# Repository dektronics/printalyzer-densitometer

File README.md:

# Printalyzer Densitometer

## Introduction

The Printalyzer Densitometer is a project whose goal is the creation of an
affordable reflection and transmission densitometer for photographic darkroom
use.

It was initially conceived as an accessory to complement the
[Printalyzer Enlarging Timer & Exposure Meter](https://github.com/dektronics/printalyzer-timer)
to ease the process of creating paper profiles. However, given the general
utility of such a device, it has been spun off as a separate project in its
own right.

A good overview of the project can be found in these blog posts:
* [The Printalyzer Densitometer Project](https://hecgeek.blogspot.com/2021/07/the-printalyzer-densitometer-project.html)

This project, using hardware tagged as "Revision C" and labeled as DPD-100, is currently shipping as an official Dektronics [product](https://www.dektronics.com/printalyzer-densitometer). Links to the user manual and regulatory compliance documents can be found on the product website.

## Project Layout

### Hardware
The "hardware" directory contains [KiCad](https://www.kicad.org/) projects
with the complete circuit schematics, bill-of-materials, and
PCB layouts.

### Software
The "software" directory contains all the source code for the firmware
that runs on the hardware.

### Enclosure
The "enclosure" directory contains any CAD models and related resources
necessary to physically assemble the device.

## License
Individual directories will contain LICENSE files as needed, with relevant
details. Generally, the hardware will be CC BY-SA and the software will be
BSD 3-Clause. However, external resources may have their own individual license terms.

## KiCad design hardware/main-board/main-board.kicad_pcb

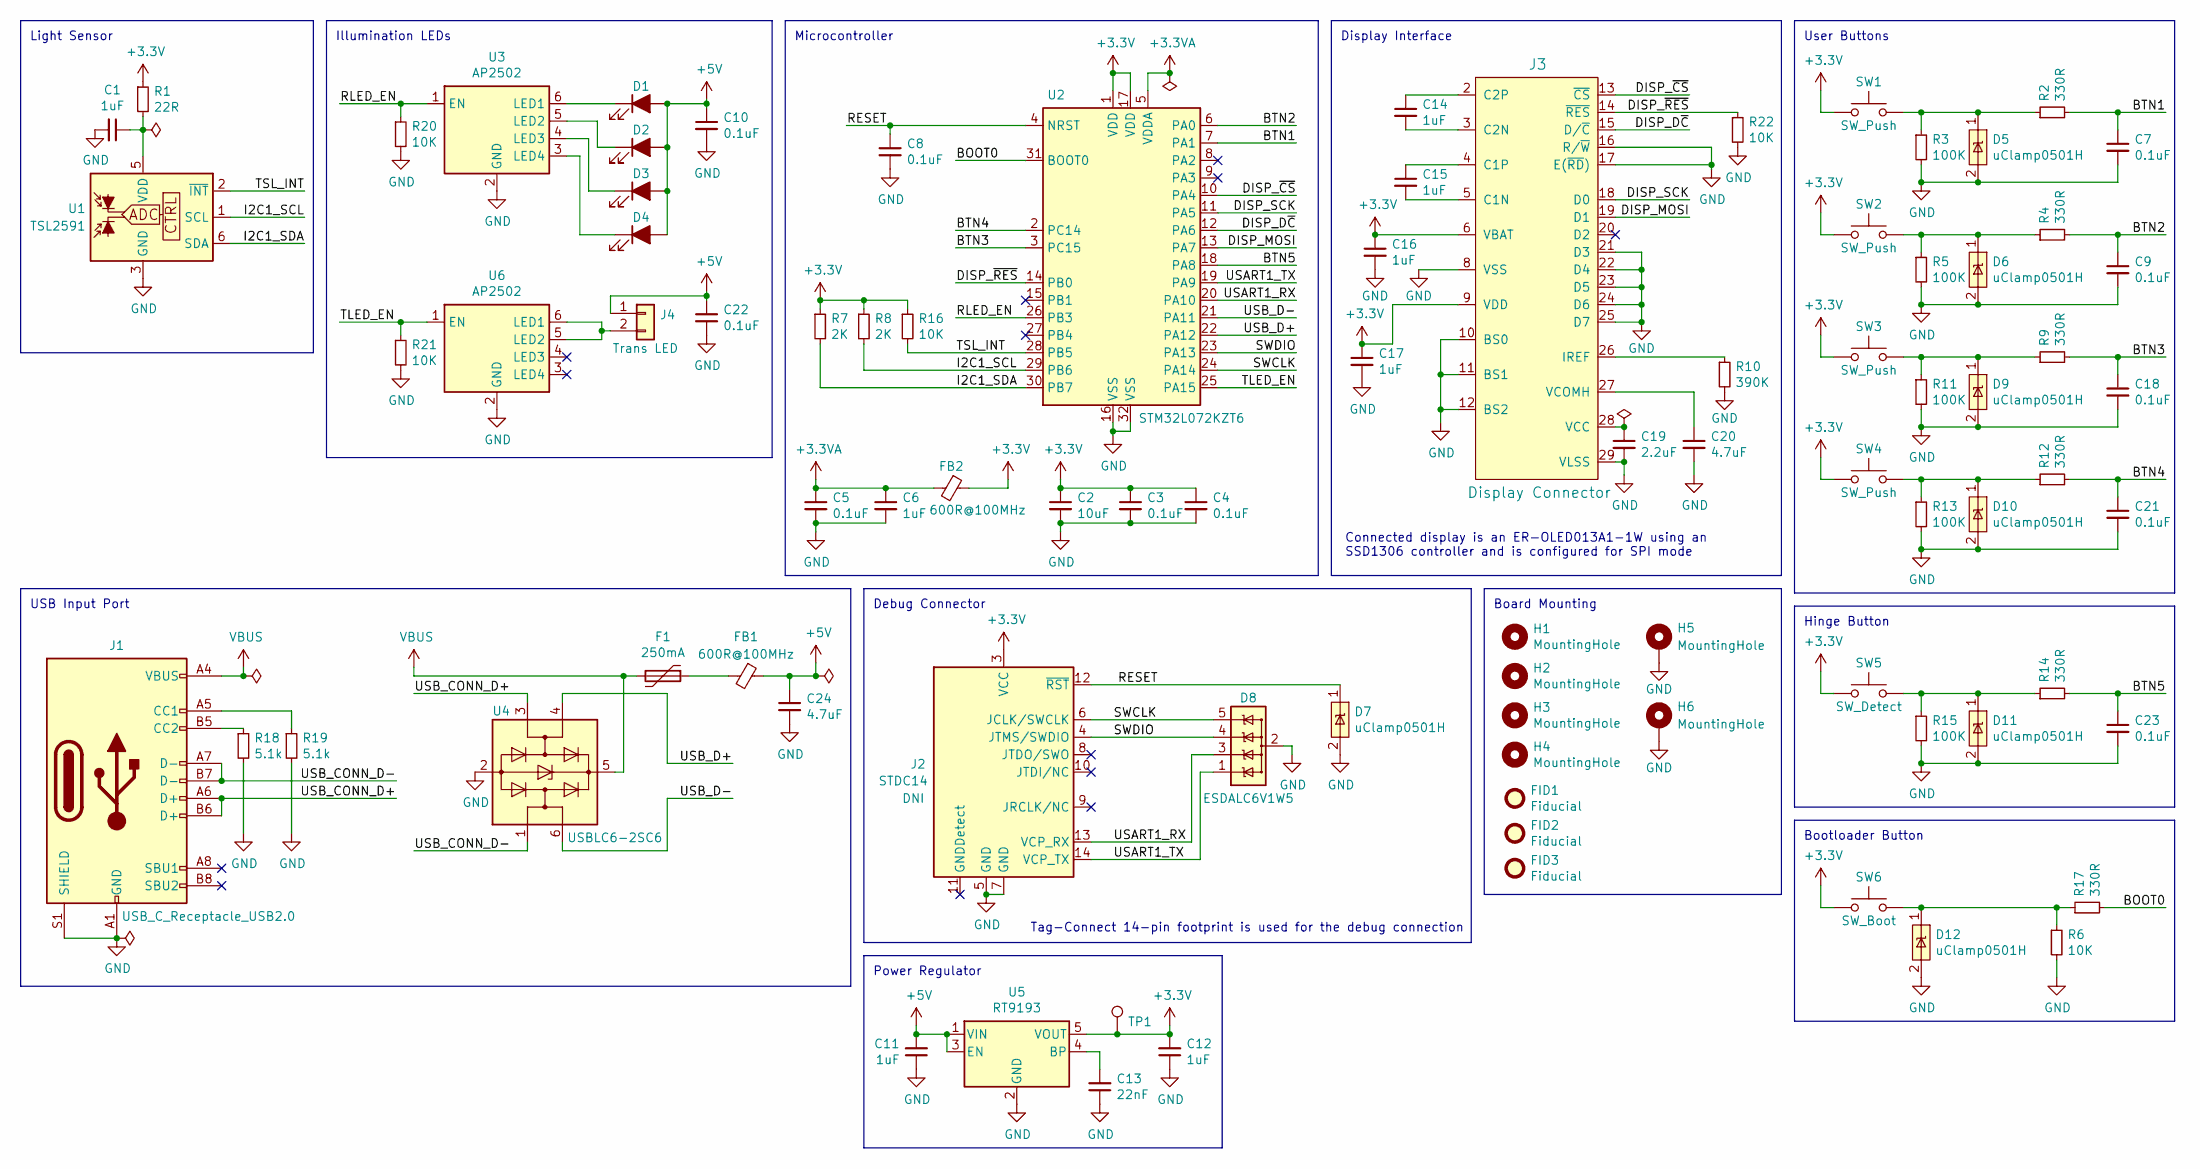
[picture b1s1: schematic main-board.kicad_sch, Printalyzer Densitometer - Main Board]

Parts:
C1: 1uF; C_0402_1005Metric; Manufacturer PN CL05A105KQ5NNNC
C2: 10uF; C_0805_2012Metric; Manufacturer PN CL21A106KAYNNNE
C3, C4, C5, C7, C8, C9, C10, C18, C21, C22, C23: 0.1uF; C_0603_1608Metric; Manufacturer PN CL10B104KA8NNNC
C6, C11, C12, C14, C15, C16, C17: 1uF; C_0603_1608Metric; Manufacturer PN CL10B105KA8NNNC
C13: 22nF; C_0805_2012Metric; Manufacturer PN C2012C0G1H223JT000N
C19: 2.2uF; C_0603_1608Metric; Manufacturer PN CL10B225KP8NNNC
C20, C24: 4.7uF; C_0603_1608Metric; Manufacturer PN CL10A475KA8NQNC
D1, D2, D3, D4: LED; LED_WL-SWTP-3022-1MP; Manufacturer PN 158302250
D5, D6, D7, D9, D10, D11, D12: uClamp0501H; D_SOD-523; Manufacturer PN UCLAMP0501H.TCT
D8: ESDALC6V1W5; SOT323-5L; Manufacturer PN ESDALC6V1W5
F1: 250mA; BF_0ZCJ_1206; Manufacturer PN 1206L025YR
FB1, FB2: 600R@100MHz; L_0603_1608Metric; Manufacturer PN MMZ1608B601CTAH0
FID1, FID2, FID3: Fiducial; Fiducial_1mm_Mask2mm
H1, H2, H3, H4: MountingHole; MountingHole_2.2mm_M2
H5, H6: MountingHole; MountingHole_2.2mm_M2_Pad_Via
J1: USB_C_Receptacle_USB2.0; USB_C_Receptacle_GCT_USB4105; Manufacturer PN USB4105-GF-A
J2: DNI; Tag-Connect_TC2070-IDC-FP_2x07_P1.27mm_Vertical; Manufacturer PN TC2070-IDC-050
J3: Display Connector; ER-CON30HT-1; Manufacturer PN ER-CON30HT-1
J4: Conn_01x02; JST_SH_BM02B-SRSS-TB_1x02-1MP_P1.00mm_Vertical; Manufacturer PN BM02B-SRSS-TB(LF)(SN)
R1: 22R; R_0402_1005Metric; Manufacturer PN AC0402JR-0722RL
R2, R4, R9, R12, R14, R17: 330R; R_0603_1608Metric; Manufacturer PN RC0603JR-07330RL
R3, R5, R11, R13, R15: 100K; R_0603_1608Metric; Manufacturer PN RC0603JR-07100KL
R6, R16, R20, R21, R22: 10K; R_0603_1608Metric; Manufacturer PN RC0603JR-0710KL
R7, R8: 2K; R_0603_1608Metric; Manufacturer PN CRCW06032K00JNEA
R10: 390K; R_0603_1608Metric; Manufacturer PN RC0603FR-07390KL
R18, R19: 5.1k; R_0603_1608Metric; Manufacturer PN RC0603JR-075K1L
SW1, SW2, SW3, SW4: SW_Push; ESwitch_TL1105_6mm_H7.5mm; Manufacturer PN TL1105SPF160Q
SW5: SW_Detect; CK_KSU213WLFG; Manufacturer PN KSU213WLFG
SW6: SW_Boot; Panasonic_EVQP7C_EVQP7L; Manufacturer PN EVQ-P7L01P
TP1: 3.3V; TestPoint_Pad_D2.0mm
U1: TSL2591; AMS_TSL2591; Manufacturer PN TSL25911FN
U2: STM32L072KZT6; ST_LQFP32; Manufacturer PN STM32L072KZT6
U3, U6: AP2502; SOT-23-6; Manufacturer PN AP2502KTR-G1
U4: USBLC6-2SC6; SOT-23-6; Manufacturer PN USBLC6-2SC6
U5: RT9193; SOT-23-5; Manufacturer PN RT9193-33GB

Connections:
+3.3V: C2.1, C3.1, C4.1, C12.2, C16.1, C17.1, FB2.1, J2.3 (VCC), J3.6 (VBAT), J3.9 (VDD), R1.1, R7.1, R8.1, R16.1, SW1.1, SW2.1, SW3.1, SW4.1, SW5.1, SW6.1, TP1.1, U2.1 (VDD), U2.17 (VDD), U5.5 (VOUT)
+3.3VA: C5.1, C6.1, FB2.2, U2.5 (VDDA)
+5V: C10.1, C11.2, C22.1, C24.1, D1.2 (A), D2.2 (A), D3.2 (A), D4.2 (A), FB1.1, J4.1, U5.1 (VIN), U5.3 (EN)
/BOOT0: R17.2, U2.31 (BOOT0)
/BTN1: C7.1, R2.2, U2.7 (PA1)
/BTN2: C9.1, R4.2, U2.6 (PA0)
/BTN3: C18.1, R9.2, U2.3 (PC15)
/BTN4: C21.1, R12.2, U2.2 (PC14)
/BTN5: C23.1, R14.2, U2.18 (PA8)
/DISP_D~C: J3.15 (D/~C), U2.12 (PA6)
/DISP_MOSI: J3.19 (D1), U2.13 (PA7)
/DISP_SCK: J3.18 (D0), U2.11 (PA5)
/DISP_~CS: J3.13 (~CS), U2.10 (PA4)
/DISP_~RES: J3.14 (~RES), R22.1, U2.14 (PB0)
/I2C1_SCL: R8.2, U1.1 (SCL), U2.29 (PB6)
/I2C1_SDA: R7.2, U1.6 (SDA), U2.30 (PB7)
/RESET: C8.1, D7.1 (IO1), J2.12 (~RST), U2.4 (NRST)
/RLED_EN: R20.1, U2.26 (PB3), U3.1 (EN)
/SWCLK: D8.5 (IO4), J2.6 (JCLK/SWCLK), U2.24 (PA14)
/SWDIO: D8.4 (IO3), J2.4 (JTMS/SWDIO), U2.23 (PA13)
/TLED_EN: R21.1, U2.25 (PA15), U6.1 (EN)
/TSL_INT: R16.2, U1.2 (~INT), U2.28 (PB5)
/USART1_RX: D8.3 (IO2), J2.13 (VCP_RX), U2.20 (PA10)
/USART1_TX: D8.1 (IO1), J2.14 (VCP_TX), U2.19 (PA9)
/USB_CONN_D+: J1.A6 (D+), J1.B6 (D+), U4.3 (I/O2)
/USB_CONN_D-: J1.A7 (D-), J1.B7 (D-), U4.1 (I/O1)
/USB_D+: U2.22 (PA12), U4.4 (I/O2)
/USB_D-: U2.21 (PA11), U4.6 (I/O1)
GND: C1.2, C2.2, C3.2, C4.2, C5.2, C6.2, C7.2, C8.2, C9.2, C10.2, C11.1, C12.1, C13.1, C16.2, C17.2, C18.2, C19.2, C20.2, C21.2, C22.2, C23.2, C24.2, D5.2 (GND), D6.2 (GND), D7.2 (GND), D8.2 (GND), D9.2 (GND), D10.2 (GND), D11.2 (GND), D12.2 (GND), H5.1, H6.1, J1.A1 (GND), J1.A12 (GND), J1.B1 (GND), J1.B12 (GND), J1.S1 (SHIELD), J2.5 (GND), J2.7 (GND), J3.8 (VSS), J3.10 (BS0), J3.11 (BS1), J3.12 (BS2), J3.16 (R/~W), J3.17 (E(~RD)), J3.21 (D3), J3.22 (D4), J3.23 (D5), J3.24 (D6), J3.25 (D7), J3.29 (VLSS), R3.2, R5.2, R6.2, R10.2, R11.2, R13.2, R15.2, R18.2, R19.2, R20.2, R21.2, R22.2, U1.3 (GND), U2.16 (VSS), U2.32 (VSS), U3.2 (GND), U4.2 (GND), U5.2 (GND), U6.2 (GND)
unnamed: C1.1, R1.2, U1.5 (VDD)
unnamed: C13.2, U5.4 (BP)
unnamed: C14.1, J3.2 (C2P)
unnamed: C14.2, J3.3 (C2N)
unnamed: C15.1, J3.4 (C1P)
unnamed: C15.2, J3.5 (C1N)
unnamed: C19.1, J3.28 (VCC)
unnamed: C20.1, J3.27 (VCOMH)
unnamed: D1.1 (K), U3.6 (LED1)
unnamed: D2.1 (K), U3.5 (LED2)
unnamed: D3.1 (K), U3.4 (LED3)
unnamed: D4.1 (K), U3.3 (LED4)
unnamed: D5.1 (IO1), R2.1, R3.1, SW1.2
unnamed: D6.1 (IO1), R4.1, R5.1, SW2.2
unnamed: D9.1 (IO1), R9.1, R11.1, SW3.2
unnamed: D10.1 (IO1), R12.1, R13.1, SW4.2
unnamed: D11.1 (IO1), R14.1, R15.1, SW5.2
unnamed: D12.1 (IO1), R6.1, R17.1, SW6.2
unnamed: F1.1, FB1.2
unnamed: J1.A5 (CC1), R19.1
unnamed: J1.B5 (CC2), R18.1
unnamed: J3.26 (IREF), R10.1
unnamed: J4.2, U6.5 (LED2), U6.6 (LED1)
VBUS: F1.2, J1.A4 (VBUS), J1.A9 (VBUS), J1.B4 (VBUS), J1.B9 (VBUS), U4.5 (VBUS)

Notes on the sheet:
Board Mounting
Illumination LEDs
Tag-Connect 14-pin footprint is used for the debug connection
Power Regulator
Display Interface
Debug Connector
USB Input Port
Bootloader Button
Light Sensor
User Buttons
Connected display is an ER-OLED013A1-1W using an SSD1306 controller and is configured for SPI mode
Microcontroller
Hinge Button

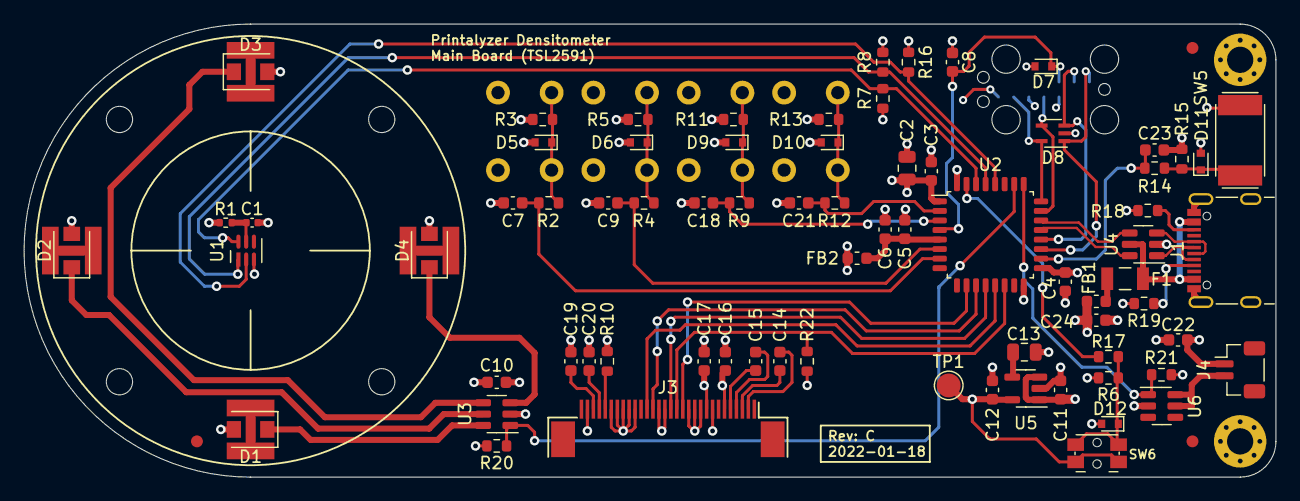
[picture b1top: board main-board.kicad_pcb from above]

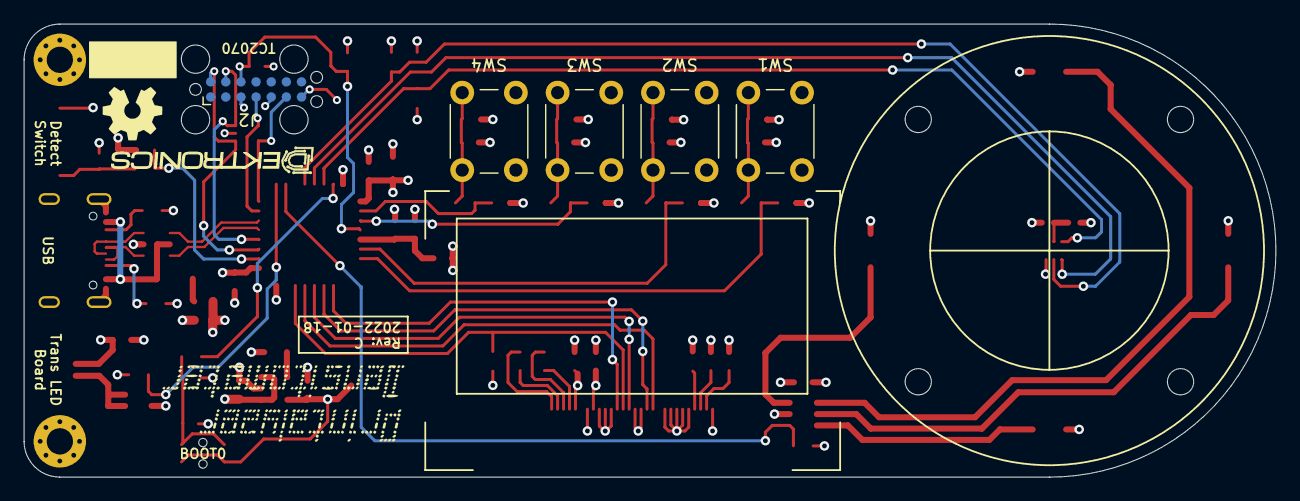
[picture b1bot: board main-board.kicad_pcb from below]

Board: 4 copper layers, 105.0 x 38.0 mm, 96 parts (9 on the bottom side), 53 nets.

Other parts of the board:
G1: LOGO; Printalyzer-logo-16_9mm
G2: LOGO; densitometer-logo-16_9mm
G4: OSHW-logo_5mm
LOGO: G3; Dektronics-logo
REF1, REF2, REF4, REF5, REF6: Tab

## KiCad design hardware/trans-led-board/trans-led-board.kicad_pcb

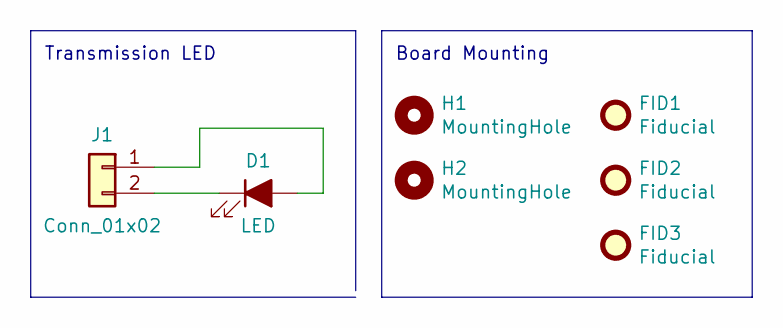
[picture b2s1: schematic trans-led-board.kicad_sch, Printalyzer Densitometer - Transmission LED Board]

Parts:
D1: LED; LED_WL-SWTP-3022-1MP_ThermalVias; Manufacturer PN 158302250
FID1, FID2, FID3: Fiducial; Fiducial_1mm_Mask2mm
H1, H2: MountingHole; MountingHole_2.2mm_M2
J1: Conn_01x02; JST_SH_SM02B-SRSS-TB_1x02-1MP_P1.00mm_Horizontal; Manufacturer PN SM02B-SRSS-TB(LF)(SN)

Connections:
unnamed: D1.1 (K), J1.2
unnamed: D1.2 (A), J1.1

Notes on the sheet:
Board Mounting
Transmission LED

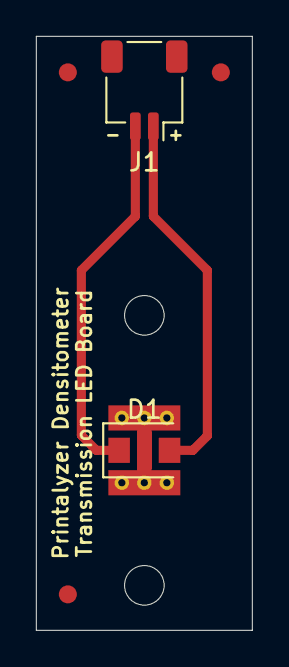
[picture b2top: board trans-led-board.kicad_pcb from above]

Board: 2 copper layers, 12.0 x 33.0 mm, 8 parts (1 on the bottom side), 2 nets.

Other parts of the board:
LOGO: G1; Dektronics-logo

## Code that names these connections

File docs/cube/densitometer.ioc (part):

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Mcu.Name=STM32L072K(B-Z)Tx
Mcu.Package=LQFP32
Mcu.UserName=STM32L072KZTx
PA0.GPIOParameters=GPIO_Label,GPIO_ModeDefaultEXTI
PA0.GPIO_Label=BTN2
PA0.GPIO_ModeDefaultEXTI=GPIO_MODE_IT_RISING_FALLING
PA0.Signal=GPXTI0
PA1.GPIOParameters=GPIO_Label,GPIO_ModeDefaultEXTI
PA1.GPIO_Label=BTN1
PA1.GPIO_ModeDefaultEXTI=GPIO_MODE_IT_RISING_FALLING
PA1.Signal=GPXTI1
PA10.Mode=Asynchronous
PA10.Signal=USART1_RX
PA11.Mode=Device
PA11.Signal=USB_DM
PA12.Mode=Device
PA12.Signal=USB_DP
PA13.Mode=Serial_Wire
PA13.Signal=SYS_SWDIO
PA14.Mode=Serial_Wire
PA14.Signal=SYS_SWCLK
PA15.GPIOParameters=GPIO_Label
PA15.GPIO_Label=TLED_EN
PA15.Signal=S_TIM2_CH1
PA4.GPIOParameters=PinState,GPIO_Label
PA4.GPIO_Label=DISP_CS
PA4.PinState=GPIO_PIN_SET
PA4.Signal=GPIO_Output
PA5.GPIOParameters=GPIO_Label
PA5.GPIO_Label=DISP_SCK
PA5.Mode=TX_Only_Simplex_Unidirect_Master
PA5.Signal=SPI1_SCK
PA6.GPIOParameters=GPIO_Label
PA6.GPIO_Label=DISP_DC
PA6.Signal=GPIO_Output
PA7.GPIOParameters=GPIO_Label
PA7.GPIO_Label=DISP_MOSI
PA7.Mode=TX_Only_Simplex_Unidirect_Master
PA7.Signal=SPI1_MOSI
PA8.GPIOParameters=GPIO_Label,GPIO_ModeDefaultEXTI
PA8.GPIO_Label=BTN5
PA8.GPIO_ModeDefaultEXTI=GPIO_MODE_IT_RISING_FALLING
PA8.Signal=GPXTI8
PA9.Mode=Asynchronous
PA9.Signal=USART1_TX
PB0.GPIOParameters=GPIO_Label
PB0.GPIO_Label=DISP_RES
PB0.Signal=GPIO_Output
PB3.GPIOParameters=GPIO_Label
PB3.GPIO_Label=RLED_EN
PB3.Signal=S_TIM2_CH2
PB5.GPIOParameters=GPIO_Label,GPIO_ModeDefaultEXTI
PB5.GPIO_Label=SENSOR_INT
PB5.GPIO_ModeDefaultEXTI=GPIO_MODE_IT_FALLING
PB5.Signal=GPXTI5
PB6.Mode=I2C
PB6.Signal=I2C1_SCL
PB7.Mode=I2C
PB7.Signal=I2C1_SDA
PC14-OSC32_IN.GPIOParameters=GPIO_Label,GPIO_ModeDefaultEXTI
PC14-OSC32_IN.GPIO_Label=BTN4
PC14-OSC32_IN.GPIO_ModeDefaultEXTI=GPIO_MODE_IT_RISING_FALLING
PC14-OSC32_IN.Signal=GPXTI14
PC15-OSC32_OUT.GPIOParameters=GPIO_Label,GPIO_ModeDefaultEXTI
PC15-OSC32_OUT.GPIO_Label=BTN3
PC15-OSC32_OUT.GPIO_ModeDefaultEXTI=GPIO_MODE_IT_RISING_FALLING
PC15-OSC32_OUT.Signal=GPXTI15
RCC.SYSCLKFreq_VALUE=32000000
RCC.SYSCLKSource=RCC_SYSCLKSOURCE_PLLCLK
board=custom

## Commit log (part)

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2021-06-01 Add initial project readme
2021-06-01 Removed symbols for components that won't be used in this project
2021-06-02 Updated display connector symbol for improved layout
    This first pass at reorganization is based on the symbols in the
    ER-OLED013 interfacing document.
2021-06-07 Add footprint and model for PTC fuse
2021-06-08 Added some silkscreen improvements to footprint
2021-06-10 Fixed size of transmission LED board
    Mistakenly used diameter as the radius of the reference circles.
2021-06-13 Change MCU component value to 64KB flash variant
2021-07-02 Initial import of CubeMX code generator dump
2021-07-03 Added code for TinyUSB
    Source: https://github.com/hathach/tinyusb
    Commit: 681a61d (about a month past 0.10.1)
2021-07-08 Initial implementation of reflection measurements
    Implementation of measurement and calibration is still being done
    through the CDC protocol handler. Eventually it will be refactored to
    somewhere else, and also hooked up to a local UI.
    Also started to add a separate document to describe the CDC serial
    protocol, so that there is a reference outside of the code itself. It
    will be expanded and fleshed out over time.
2021-07-13 Main screen measurement animations
2021-07-13 Clamp output display values within device limits
2021-07-20 Added latest CAD and STL files for the enclosure
    This is still very much a work in progress, but the design will most
    likely look like this.
2021-08-02 Add ability to display negative density values
    This will be used when we add the ability to "zero" on a reference
    target (such as film/paper base) to indicate that the user has measured
    something below that point's value.
2021-08-30 Switch single-line TVS diode components
    Switch the existing single-line TVS diodes to a slightly larger
    component.
    Refs #10
2021-08-30 Add footprint for Panasonic EVQP7 switches
2021-09-08 Clean up Fab layers to make them less full of noise
2021-09-21 Change script shell to explicitly run with bash
2021-09-24 Initial FreeRTOS task-based startup integration
    Created a central module to handle starting FreeRTOS tasks for all major
    functions. This puts all the task definitions in one place, and starts
    tasks in sequence using a semaphore to keep initialization behavior
    predictable.
    The currently-implemented tasks include:
    - Main Task
2021-09-29 Convert sensor diag screen to use new task interface
2021-10-05 Updated tinyUSB to latest post-0.11.0 code
    Based on checkout tag:
    d9bda631d4ce7e82322a5a71339c2556d410c1e0
    This is a little over a month past the 0.11.0 release.
2021-10-06 Replaced newlib printf with mpaland printf across the code
    This is mostly a stdio.h to printf.h search and replace, in the main
    firmware code and some bits of easylogger.
    There still may be more cruft to hunt down later on.
    Making this change should give us more control over string formatting,
    and make it possible to use more robust formatting of floating point
    values.
2021-10-07 Move some values to constants, and increase the max trans reading
2021-10-11 Added error handling paths to sensor task commands
    All sensor tasks now have a response code. Since external commands are
    typically handled synchronously, the response code is populated as part
    of the process of handling that command.
    Also added code to check this response code, so that failures inside the
    sensor task now propagate upward.
    Fixes #13
2021-10-16 Fixed some error logging issues
2021-10-18 Update sensor read loop to standardize on-to-read time
    To manage LED brightness drop-off effects, the amount of time from
    turning the LED on to taking a reading should be constant, regardless of
    what needs to happen in the measurement loop.
    One way of doing this is by assuming we'll only ever need two gain
    settings (high and max), and that we can pick our gain independently
    from taking our actual readings.
2021-10-21 Added slope correction to density readings
    This includes a step that uses the slope correction values,
    and also changes the extended CDC data format to include both corrected
    and uncorrected raw readings.
    Refs #12
2021-10-25 Remove support for non-HEX-encoded floating point commands
    With the exception of the basic density reading output format, the
    USB-CDC interface is intended for use with a dedicated desktop
    application or utility. There is no longer any need to keep this
    interface usable by a human who does not have access to such a utility.
    The encoded hex format is much easier to handle consistently than
    human-readable floating point formats, and requires less library code
2021-11-05 Implemented a UF2 bootloader to ease the firmware update process
    This bootloader is substantially derived from the TinyUF2 project, and
    tries very hard to fit within 16k of space at the start of flash.
    To achieve this, it has to be compiled with -flto and it cannot have
    display output enabled at the same time as UART-based debug logging.
    The display output implementation is extremely minimal, and contains all
    of its image assets in the form of data already prepared to be written
2021-11-09 Main window layout tweaking
2021-11-15 Update LED footprints for thermal properties
    Fixes naming convention of thermally-enhanced LED footprints to be
    closer to the KiCad convention, and separates into two versions. One
    with thermal vias and one without.
    Updated transmission board metadata to referene the correct new
    footprint name.
    Updated main board to use the new version of the new footprint without
2021-11-16 Updated footprints for LQFP-32 and USB-C connector
    LQFP-32 footprint is based on the stock footprint, modified according to
    the recommended footprint in ST's datasheet. This reduces the length of
    the pads under the leads, which may help reduce bridging.
    USB-C footprint is based on the stock Palcon footprint, modified
    according to the GCT datasheet. This is several very minor changes, that
    might not even make much of a difference.
2021-11-30 Update schematic properties
    Changed all revision labeling to "C" with today's date. This is subject
    to change when the boards are sent for manufacturing, but removing
    placeholders make mistakes here less likely in the future.
    Set grid and drill origins to what they're hopefully supposed to be. Not
    sure how much this matters, but it probably won't hurt.
    More layout nitpicking and review changes may happen between now and
2022-01-03 Migrate project from KiCad v5 to v6
    - Update symbol library files for KiCad 6
    - Moved location of symbol datasheet elements, since v6 suddenly decided
    they should always be visible in the symbol editor
    - Update transmission LED board for KiCad 6
    - No real changes needed here, just the automated conversion and cleanup
    - Also adjusted silkscreen rev/date fields to use variables
2022-01-06 Update CubeMX specs to reassign LED enable pins
    The original assignments for the LED enable pins (TLED_EN and RLED_EN)
    are used by USART2 when the system bootloader is invoked.
    This means that all of our measurement LEDs would switch on at full
    power, if the device was booted into USB DFU mode for out-of-band
    firmware updates.
    While not technically a problem for normal users, allowing this does
2022-01-15 Make panelize targets depend on relevant config files
2022-01-29 Update schematic BOM data based on actual parts ordered
    Several components have changed suppliers and/or manufacturers between
    the initial design prototypes and the bulk component orders. This
    changes BOM data to reflect that.
2022-02-04 Upgrade TinyUSB stack to 0.12.0-316-gd6fb1859
2022-02-13 Fix preprocessor guard around light test routines
2022-02-17 Add use of constant
2022-02-25 Initial implementation of diag remote control panel
    This implements a GUI around the remote control commands currently
    implemented on the device. It provides an easy way to control LED state
    and the sensor read task.
    To be truely useful for many testing/characterization use cases, a
    number of modifications will be needed to the remote-controllable sensor
    loop interface. However, right now this implements the interface as it
2022-02-27 Change ADC handler to use LL header for various macros
    The ADC LL header, which was not included in our initial CubeMX dump,
    contains various macros for ADC constants and calculations. We should
    switch to using those, rather than our own attempt at duplicating them,
    to clean things up a bit.
2022-03-14 Update build settings for new CubeIDE version
    The lastest update no longer generates the bin output files by default,
    and we depend on them.
2022-03-21 Update USB-CDC interface to transmit zero offset information
    This makes it possible for a desktop app, using the extended output
    format, to be aware of zero offset settings applied to density readings.
    Refs #19
2022-03-23 Set various Qt application properties
2022-03-30 Reorganize directory structure of desktop app and add icon
    This is the first step to incorporating deployment changes into the
    project. It introduces a structure to the source tree that can be added
    to, and also brings in an icon.
    Then icon is currently based on a colored wireframe drawing of the
    device, and is probably the best we can do without a graphic designer
    being brought in.
2022-04-22 Added EMC cycle test driver to the desktop app
2022-05-12 Update u8g2 to 2.29.11-334-g29c6b797
    The changes in this version seem to mostly be fonts that aren't in use,
    and support for devices that aren't in use. Just doing it as a periodic
    task to keep future updates less dramatic.
2022-05-27 Version label update for beta release of firmware
2022-06-05 Remove debug output for function
2022-07-01 More board data updates for fabrication
    Updated various origin locations for consistency
    Did a zone refill on the main board
    Changed panel sizes per assembly house recommendations
2022-07-11 Hid unused menu item and bumped version information
2022-08-26 Add command line functionality for info query and settings export
    This adds in the initial framework for supporting actual command-line
    interaction with the desktop app, as a starting point for no longer
    needing hand-hacked separate "bench test" apps for automation use cases.
    It includes an alternative class to the main window, which handles
    command execution and response during command-line operation.
    Two commands have been added so far. First, a basic system information
2022-08-29 Update app version in descriptor
2022-10-26 Change PWM frequency used for controlling LED brightness
    This adjusts the timer prescaler value to change the PWM frequency from
    125kHz down to 41.667kHz.
    The reason for this change is that with the old frequency, at
    sufficiently high duty cycle values, the low portion of the pulse did
    not always drop below the LED driver's 0.5V threshold and did not stay
    there for at least 100ns.
2022-11-28 Switch all single-line TVS diodes to the Semtech uClamp3301H
    The ST diodes used in the original design had two main problems:
    - Their package size made handling and manufacturability difficult,
    resulting in a lot of spotted issues on production boards
    - Their rating can only protect 5V-tolerant lines, and a few of the
    buttons are actually connected on MCU pins that may only be 3.3V
    tolerant
2023-06-01 Update HAL/FW code to FW_L0 1.12.2
    Refs #49
2023-06-02 Add ability to display alternative decimal separators
    Refs #51
